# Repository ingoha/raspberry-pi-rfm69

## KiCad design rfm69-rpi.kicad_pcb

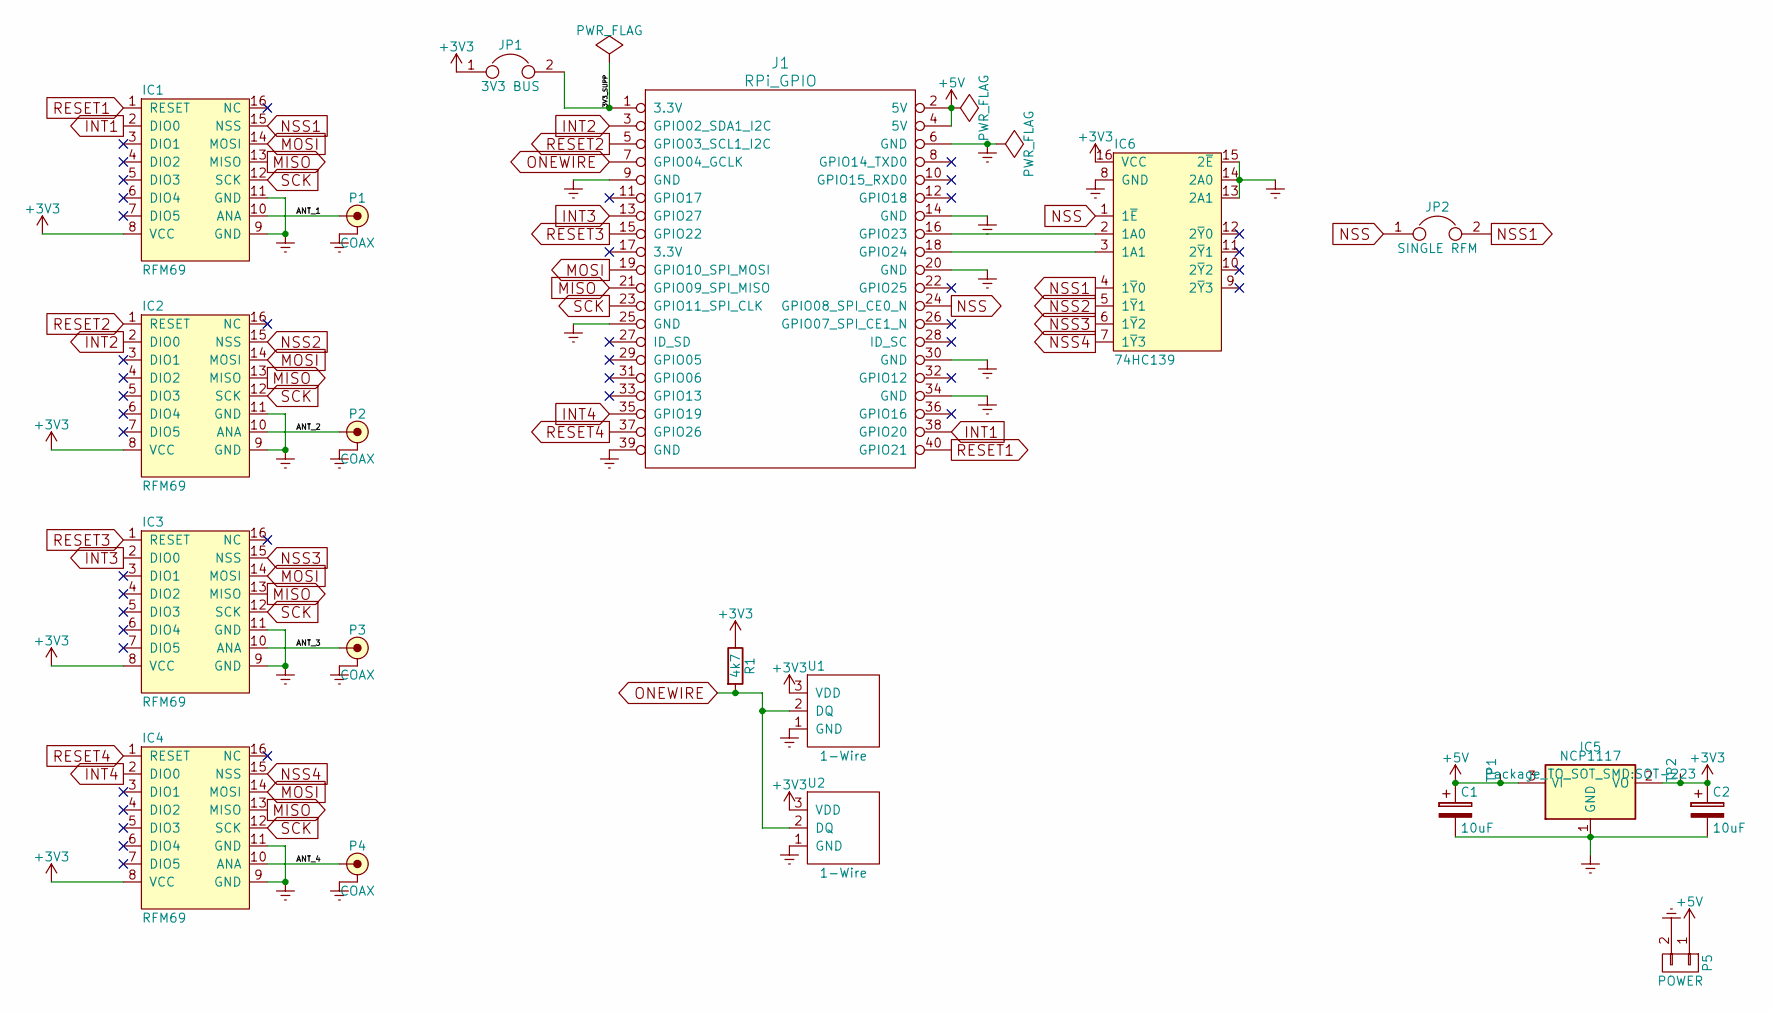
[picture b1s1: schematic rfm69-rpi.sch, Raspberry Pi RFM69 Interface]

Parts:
C1, C2: 10uF; C_0805
IC1, IC2, IC3, IC4: RFM69
IC5: NCP1117; SOT-223
IC6: 74HC139; TSSOP-16; Farnell 2444981
J1: RPi_GPIO; raspberrypi2
JP1: 3V3 BUS; TESTPT
JP2: SINGLE RFM; TESTPT
P1, P2, P3, P4: COAX; SMA-EDGE; Farnell 1608592
P5: POWER; JST-PH-SM4-2
R1: 4k7; 0805
TP1, TP2: TESTPAD
U1, U2: 1-Wire; TO-92_Molded_Narrow

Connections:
+3V3: C2.1, IC1.8 (VCC), IC2.8 (VCC), IC3.8 (VCC), IC4.8 (VCC), IC5.2 (VO), IC6.16 (VCC), JP1.1, R1.1, TP2.1, U1.3 (VDD), U2.3 (VDD)
+5V: C1.1, IC5.3 (VI), J1.2 (5V), J1.4 (5V), P5.1, TP1.1
/3V3_SUPP: J1.1 (3.3V), JP1.2
/ANT_1: IC1.10 (ANA), P1.1 (RF)
/ANT_2: IC2.10 (ANA), P2.1 (RF)
/ANT_3: IC3.10 (ANA), P3.1 (RF)
/ANT_4: IC4.10 (ANA), P4.1 (RF)
Earth: C1.2, C2.2, IC1.9 (GND), IC1.11 (GND), IC2.9 (GND), IC2.11 (GND), IC3.9 (GND), IC3.11 (GND), IC4.9 (GND), IC4.11 (GND), IC5.1 (GND), IC6.8 (GND), IC6.13 (2A1), IC6.14 (2A0), IC6.15 (2~E), J1.6 (GND), J1.9 (GND), J1.14 (GND), J1.20 (GND), J1.25 (GND), J1.30 (GND), J1.34 (GND), J1.39 (GND), P1.2 (GND), P2.2 (GND), P3.2 (GND), P4.2 (GND), P5.2, U1.1 (GND), U2.1 (GND)
INT1: IC1.2 (DIO0), J1.38 (GPIO20)
INT2: IC2.2 (DIO0), J1.3 (GPIO02_SDA1_I2C)
INT3: IC3.2 (DIO0), J1.13 (GPIO27)
INT4: IC4.2 (DIO0), J1.35 (GPIO19)
MISO: IC1.13 (MISO), IC2.13 (MISO), IC3.13 (MISO), IC4.13 (MISO), J1.21 (GPIO09_SPI_MISO)
MOSI: IC1.14 (MOSI), IC2.14 (MOSI), IC3.14 (MOSI), IC4.14 (MOSI), J1.19 (GPIO10_SPI_MOSI)
NSS: IC6.1 (1~E), J1.24 (GPIO08_SPI_CE0_N), JP2.1
NSS1: IC1.15 (NSS), IC6.4 (1~Y~0), JP2.2
NSS2: IC2.15 (NSS), IC6.5 (1~Y~1)
NSS3: IC3.15 (NSS), IC6.6 (1~Y~2)
NSS4: IC4.15 (NSS), IC6.7 (1~Y~3)
unnamed: IC6.2 (1A0), J1.16 (GPIO23)
unnamed: IC6.3 (1A1), J1.18 (GPIO24)
ONEWIRE: J1.7 (GPIO04_GCLK), R1.2, U1.2 (DQ), U2.2 (DQ)
RESET1: IC1.1 (RESET), J1.40 (GPIO21)
RESET2: IC2.1 (RESET), J1.5 (GPIO03_SCL1_I2C)
RESET3: IC3.1 (RESET), J1.15 (GPIO22)
RESET4: IC4.1 (RESET), J1.37 (GPIO26)
SCK: IC1.12 (SCK), IC2.12 (SCK), IC3.12 (SCK), IC4.12 (SCK), J1.23 (GPIO11_SPI_CLK)

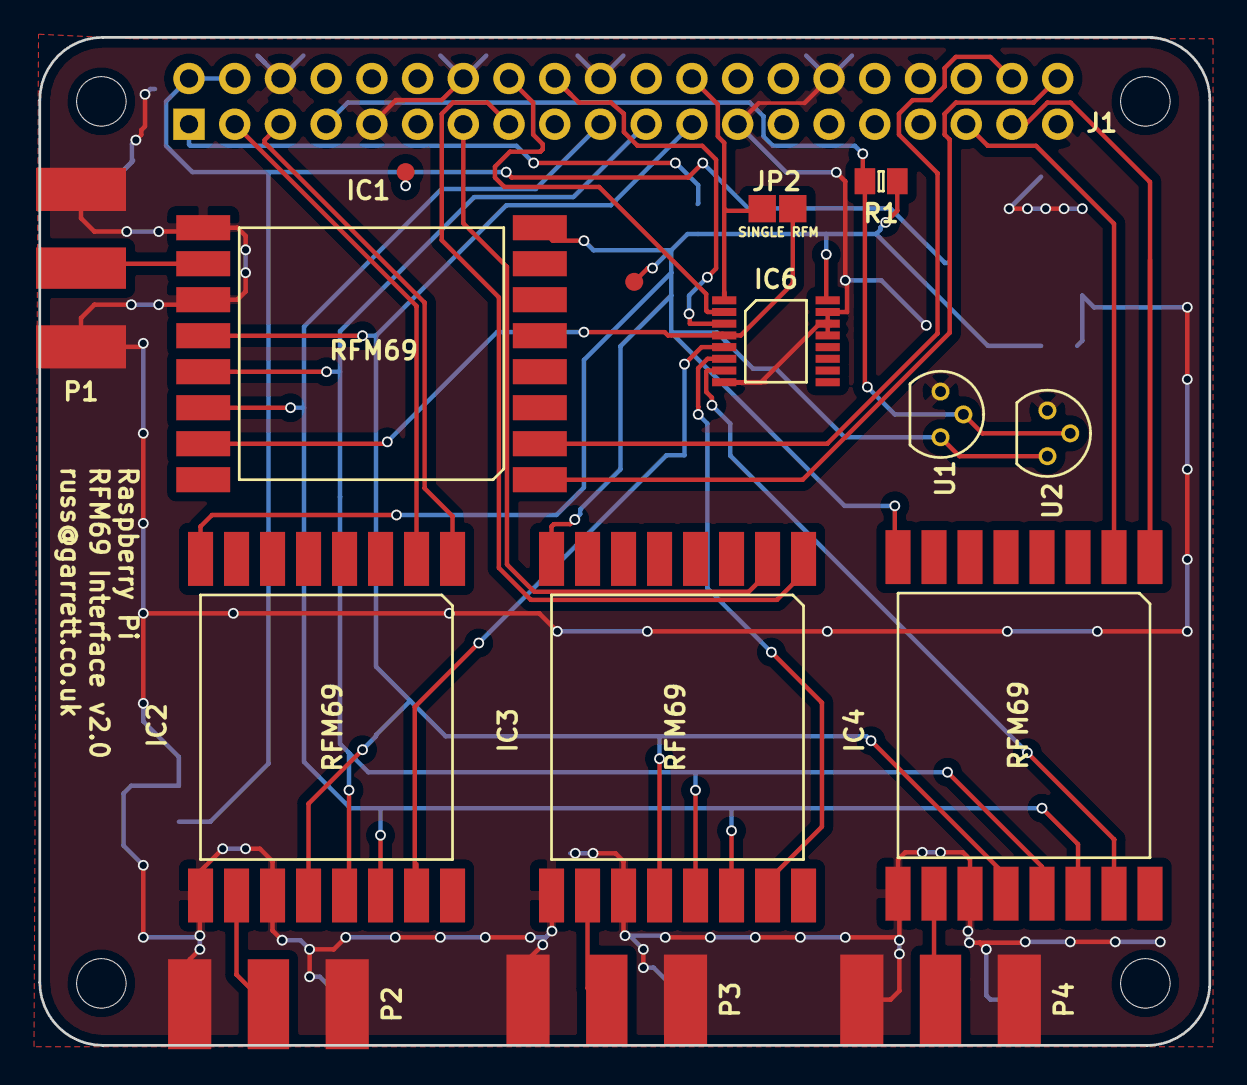
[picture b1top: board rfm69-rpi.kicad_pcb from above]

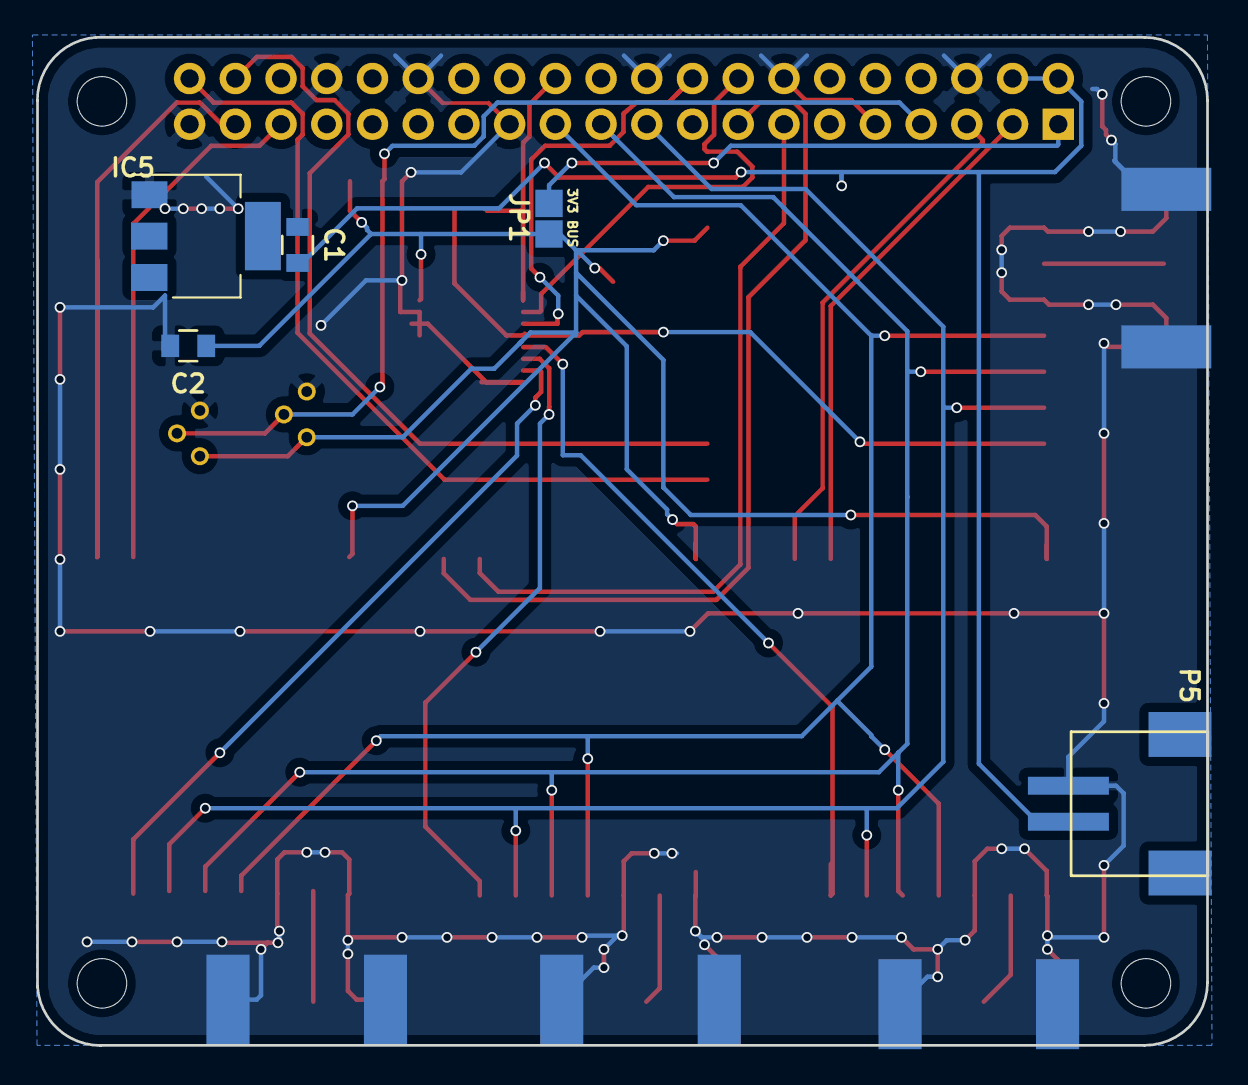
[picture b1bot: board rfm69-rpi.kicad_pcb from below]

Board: 2 copper layers, 65.0 x 56.0 mm, 21 parts (5 on the bottom side), 27 nets.

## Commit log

2020-04-29 Converted to Kicad 5 format; changed direction of INT1
2020-04-29 Fixed RPi footprint
2020-04-29 Finally fixed footprint.
2020-04-29 Tuned gerber options
2020-04-29 Fixed gerber options (for JLCPCB).
2020-04-29 Removed something
